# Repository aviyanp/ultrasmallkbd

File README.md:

# ultrasmallkbd
a small staggered qwerty keyboard with only the necessities

I made this mostly in order to use as a portable text entry solution instead of lugging around a keyboard around, especially if I want to type things into my smart TV or simply can't find a keyboard anywhere.

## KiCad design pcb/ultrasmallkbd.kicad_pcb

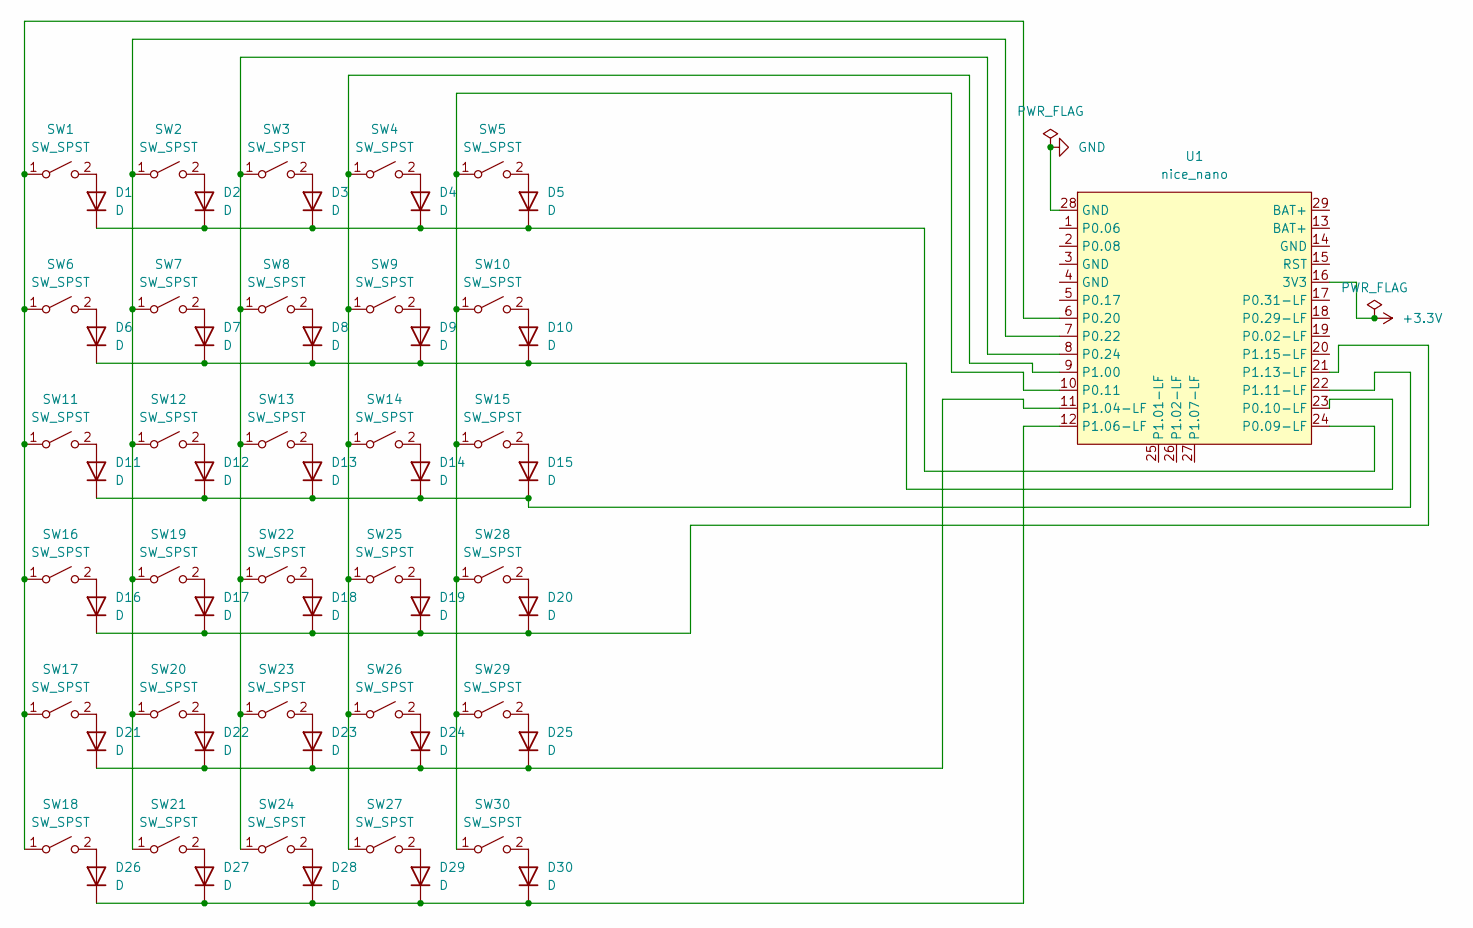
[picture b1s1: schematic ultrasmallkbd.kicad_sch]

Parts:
D1, D2, D3, D4, D5, D6, D7, D8, D9, D10, D11, D12, D13, D14, D15, D16, D17, D18, D19, D20, D21, D22, D23, D24, D25, D26, D27, D28, D29, D30: D; SOD-123_VISHAY
SW1, SW2, SW3, SW4, SW5, SW6, SW7, SW8, SW9, SW10, SW11, SW12, SW13, SW14, SW15, SW16, SW17, SW18, SW19, SW20, SW21, SW22, SW23, SW24, SW25, SW26, SW27, SW28, SW29, SW30: SW_SPST; SW_TS-1088-AR02016
U1: nice_nano; nice_nano_AH_USBup

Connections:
+3.3V: U1.16 (3V3)
GND: U1.3 (GND), U1.4 (GND), U1.14 (GND), U1.28 (GND)
unnamed: D1.2 (A), SW1.2 (B)
unnamed: D1.1 (K), D2.1 (K), D3.1 (K), D4.1 (K), D5.1 (K), U1.24 (P0.09-LF)
unnamed: D2.2 (A), SW2.2 (B)
unnamed: D3.2 (A), SW3.2 (B)
unnamed: D4.2 (A), SW4.2 (B)
unnamed: D5.2 (A), SW5.2 (B)
unnamed: D6.2 (A), SW6.2 (B)
unnamed: D7.2 (A), SW7.2 (B)
unnamed: D8.2 (A), SW8.2 (B)
unnamed: D9.2 (A), SW9.2 (B)
unnamed: D10.2 (A), SW10.2 (B)
unnamed: D6.1 (K), D7.1 (K), D8.1 (K), D9.1 (K), D10.1 (K), U1.23 (P0.10-LF)
unnamed: D11.2 (A), SW11.2 (B)
unnamed: D11.1 (K), D12.1 (K), D13.1 (K), D14.1 (K), D15.1 (K), U1.22 (P1.11-LF)
unnamed: D12.2 (A), SW12.2 (B)
unnamed: D13.2 (A), SW13.2 (B)
unnamed: D14.2 (A), SW14.2 (B)
unnamed: D15.2 (A), SW15.2 (B)
unnamed: D16.2 (A), SW16.2 (B)
unnamed: D16.1 (K), D17.1 (K), D18.1 (K), D19.1 (K), D20.1 (K), U1.21 (P1.13-LF)
unnamed: D17.2 (A), SW19.2 (B)
unnamed: D18.2 (A), SW22.2 (B)
unnamed: D19.2 (A), SW25.2 (B)
unnamed: D20.2 (A), SW28.2 (B)
unnamed: D21.2 (A), SW17.2 (B)
unnamed: D21.1 (K), D22.1 (K), D23.1 (K), D24.1 (K), D25.1 (K), U1.11 (P1.04-LF)
unnamed: D22.2 (A), SW20.2 (B)
unnamed: D23.2 (A), SW23.2 (B)
unnamed: D24.2 (A), SW26.2 (B)
unnamed: D25.2 (A), SW29.2 (B)
unnamed: D26.2 (A), SW18.2 (B)
unnamed: D26.1 (K), D27.1 (K), D28.1 (K), D29.1 (K), D30.1 (K), U1.12 (P1.06-LF)
unnamed: D27.2 (A), SW21.2 (B)
unnamed: D28.2 (A), SW24.2 (B)
unnamed: D29.2 (A), SW27.2 (B)
unnamed: D30.2 (A), SW30.2 (B)
unnamed: SW1.1 (A), SW6.1 (A), SW11.1 (A), SW16.1 (A), SW17.1 (A), SW18.1 (A), U1.6 (P0.20)
unnamed: SW5.1 (A), SW10.1 (A), SW15.1 (A), SW28.1 (A), SW29.1 (A), SW30.1 (A), U1.10 (P0.11)
unnamed: SW2.1 (A), SW7.1 (A), SW12.1 (A), SW19.1 (A), SW20.1 (A), SW21.1 (A), U1.7 (P0.22)
unnamed: SW3.1 (A), SW8.1 (A), SW13.1 (A), SW22.1 (A), SW23.1 (A), SW24.1 (A), U1.8 (P0.24)
unnamed: SW4.1 (A), SW9.1 (A), SW14.1 (A), SW25.1 (A), SW26.1 (A), SW27.1 (A), U1.9 (P1.00)

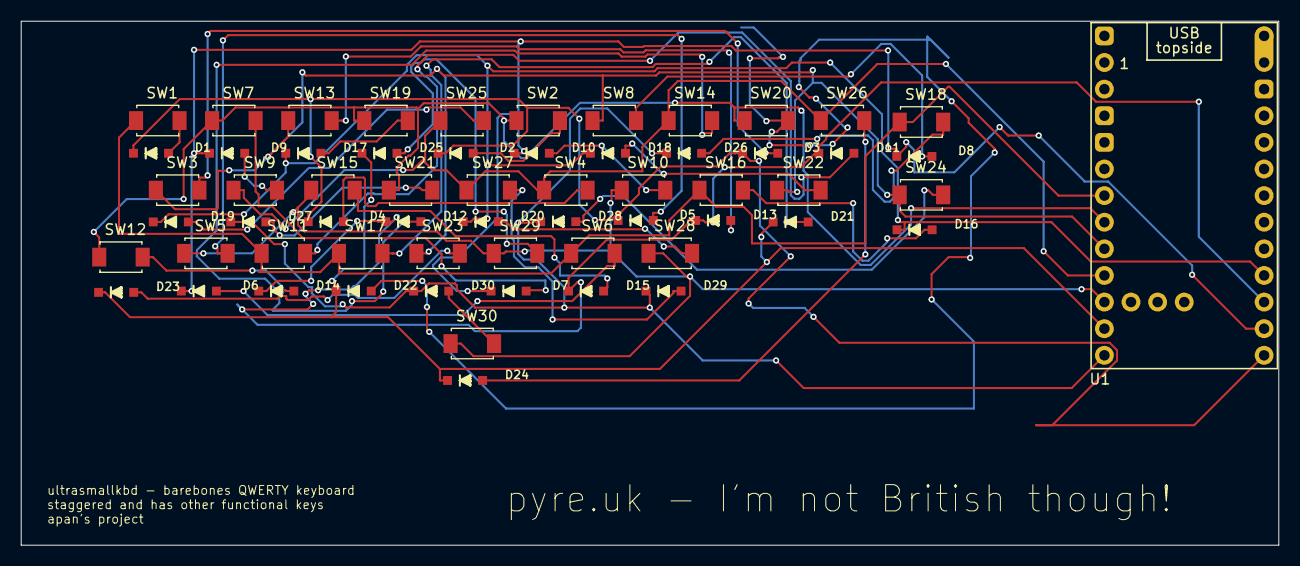
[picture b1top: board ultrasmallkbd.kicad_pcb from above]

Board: 2 copper layers, 120.0 x 50.0 mm, 61 parts (0 on the bottom side), 42 nets.

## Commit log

2025-06-29 heh
    PCB Files for KiCAD
